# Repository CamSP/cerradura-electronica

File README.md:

# Cerradura electrónica

## Descripción del producto
El producto consiste en una cerradura electrónica casera de alta seguridad, la cuál permitirá al usuario tener 3 niveles de autenticación distintos para acceder a ella. También cuenta con la opción de registar más de un usuario previamente registrado en una base de datos. Los sensores encargados para la debida autenticación de los usuarios son: 

* Reconocimiento facial
* Huella dactilar
* Sistema RFID por tarjeta

El sistema implementará la huella dactilar y el RFID en la carcasa de la cerradura. Para el reconocimiento facial se hará uso de una aplicación con el fin de simplificar los requerimientos de hardware del producto. Adicionalmente, en la aplicación se administrará la cerradura, lo que incluye los usuarios registrados y huellas registradas en esta. Se puede configurar la cerradura para tener una única o una doble autentificación en caso de que se necesiten mayores restricciones para el manejo de la cerradura.
El elemento diferencial de nuestro producto a los demás sistemas que se encuentran en el mercado es la experiencia personal al hacer uso de varios sistemas biométricos y una aplicación que permiten al usuario interactuar de manera directa con la cerradura. Adicionalemnte, nuestro producto incluye más periféricos que las que se encuentran en el mercado, esto causa una diversificación en el uso del sistema. Otro vlor añadido es el costo vs prestaciones, ya que en el mercado cerraduras biométricas son costosas y solo poseen el lector de huellas como módulo de seguridad.

## Requerimientos funcionales
* Uso de cerradura electrónica para controlar la apertura de la puerta.
* Reconocimiento facial desde el teléfono como alternativa para abrir o cerrar la cerradura.
* Reconocimiento de huellas dactilares.
* Comunicación con base de datos remota a través de WiFi.
* Comunicación con dispositivos a través de bluetooth
* La lectura de huella dactilar y el reconocimiento facial puede realizarse por medio de la aplicación móvil.
* En caso de que haya un corte en la energía, el sistema seguirá funcionando con baterias.

## Requerimientos no funcionales
* Debido al uso de la cerradura electrónica, la cerradura mecánica convencional no es necesaria, sin embargo, en caso de que el cliente lo desee, se pueden usar en conjunto.
* Los usuarios registrados de cada cerradura no pueden ser vistos/usados por usuarios externos al propietario.
* El producto debe adaptarse a diferentes tipos de cerraduras.
* El sistema de autenticación remoto debe poder ser utilizado en la mayor cantidad de modelos de teléfonos posible.
* La aplicación móvil del dispositivo debe estar disponible en inglés y español.
* Los datos solo podrán ser cambiados por el administrador de la cerradura.
* La cerradura está pensada para uso doméstico, esto considerando que el nivel de seguridad para uso en empresas o industrias debe ser mayor.
* El sistema podrá funcionar sin necesidad de conexión a internet.
* El sistema tendra un método de autentificación para los administradores de la cerradura.
* El sistema puede repararse rapidamente cambiando uno de los modulos, ademas el daño en uno de los modulos no inhabilita el sistema.
* La caja del producto debe ser resistente a golpes.
* El sistema no podrá ser desmontado desde la parte exterior de la puerta.
* Para garantizar la seguridad de datos de los usuarios, se utilizará encriptación en la base de datos del sistema.
* En caso de cortes de energía se deshabilitarán los módulos bluetooth y WiFi para maximizar la duración de la carga de la batería.
* Se le asignará un espacio de memoria interna al dispositivo para almacenar los datos necesarios de autenticación del huella dactilar y RFID en el caso de exista un corte en la energía y no se pueda utilizar el WiFi.

## Componentes Utilizados
* Capacitores: 0.1 uF, 22 uF, 10 uF, 0.3 uF, 100 pF, 47 uF y 100 uF.
* Resistencias: 10k Ohm, 62k Ohm, 3.3k Ohm, 47k Ohm, 100 Ohm.
* Inductores: 22 uH.
* LEDs.
* Diodos Rectificadores: SS34 y 1N5406.
* Diodos.
* ESP32 - WROVER.
* Módulo RFID RC522.
* Lector de Huella AS608.
* Elevador de Voltaje MT3608.
* Regulador de Voltaje AMS1117.
* Conector 01x02.
* Conector 01x03.
* Relé Sanyou SRD Form C.
* Switch.

## Características
* Se utilizan componentes superficiales con el fin de reducir el tamaño del circuito.  
* El circuito se diseña y se programa para mininizar el gasto de energia en sí, donde el mayor gasto de la energia está en la cerradura. 
* El circuito consiste del controlador ESP32, sus protección, indicadores y conexiones a los otros periféricos, como el lector de huella.
* El diseño del circuito fue pensado para hacerse de forma modular con la cerradura y sus periféricos.

## Diseño del circuito

Primero se parte del controlador a utilizar, en este caso el esp32.
Seguidamente se determinan los módulos a utilizar, el RFID, el sensor de huella.
Con esto presente se seleccionan los pines necesarios para los módulos, además se realiza la etapa de potencia para 
la cerradura. Se realiza la pcb en kicad. Se incluyen indicadores, LEDs, para cada función (Alerta on-off, conexión establecida con cada uno de los módulos) 
Importante. El diseño también se hizo modular en el programa kicad. 
Se incluyeron los agujeros para la sujeción de la placa y se realizó la pcb en allpcb.
Se utilizaron componentes smd.

### ESP32

El controlador esp32 fue utilizado porque facilita la comunicación WiFi y Bluetooth. Además su programación es através de 
Micropython o el ide de Arduino. Esto hace rápida la programación si existen las librerías para los sensores.

### Etapa de potencia
* modulo ams1117
Regulador lineal de alta eficiencia. Dispositivo de voltaje fijo para usarlo a 3.3v con corriente maxima de 1 amperio, temperatura de trabajo de -40 150, con voltaja entrada 4.75 para una salida de 3.3. Y Pérdidas de voltaje debidas al calor.
Para una entrada de voltaje entre 4.8 y 12 V en este ams1117-3.3 se consigue 3.3 V en la salida, utilizando los capacitores recomendados por el fabricante.
* modulo mt3608
El mt3608 es un conversor DC-DC conmutado tipo boost. Trabaja de 2V a 24V en la entrada, dispositivo de voltaje de salida variable. Además de una eficiencia del 97 %. El fabricante da un circuito para aplicación basica. Este trabaja a una frecuencia fija. Para las resistencias, se utiliza la siguiente relación deacuerdo con el voltaje de entrada.
Vout=Vref*(1+R1/R2). 
Para el inductor es recomendable utilizar uno de 4.7uH a 22uH.
En cuanto a los capacitores, dos capacitores iguales de  alrededor de los 22uF.
Tambien el fabricante sugiere un diodo shcottky para no interferir con la velocidad de funcionamiento del modulo mt3608.

### Cerradura
Para el circuito de la cerradura se utiliza un rele de 3v que se conencta a una de las salidas digitales del ESP32. Entre los terminales normalmente abiertos se conecta la cerradura y 12v que la alimentan, de forma que cuando el rele se enciende se energiza la cerradura. Por otro lado, dado que el rele y la cerradura utilizan enbobinados para funcionar, es necesario proteger el circuito de posibles corrientes parasitas que estas generen una vez dejen de estar energizadas, de esta forma se conecta un diodo entre GND y la entrada digital que se conecta al rele, y otro diodo entre GND y la conexión entre el rele y la cerradura.

### RFID
Para el lector RFID se utilizó el módulo comercial que incluye el sistema de modulación y demodulación de 13.56 MHz y la respectiva antena para la lectura. El módulo se comunica por SPI por lo que puede ser utilizado con el ESP32 sin problemas. La conexión a la placa se realiza mediante una serie de puertos donde se introducen los pines del RFID; trabaja con 3.3 voltios por lo que puede ser utilizado directamente con una alimentación de 5 voltios. El pin de alimentación tiene una conexión con un condensador para proteger el módulo y de allí al relé.

### Sensor de huella

El módulo utilizado es el as608, un módulo fácil de conseguir, el cual permite una programación sensilla con las librerías existentes,
Este módulo tiene una memoria y permite guardar y verificar las huellas ingresadas, además su comunicación es serial.

### LEDS de funcionamiento

Se incluyeron LEDs como indicadores, para saber si hay batería, 
Si hay WiFi o si está abierta o cerrada la cerradura.

### Programador

La programación se hizo con micropython porque Python es un lenguaje conocido y fácil de entender, además de tener 
las librerías necesarias para el proyecto, se utizo la ide Tommy de Linux y se subieron los diferentes programas con un computador cuyo
sistema operativo es Linux. 
Para el sensor de la huella, fue necesario buscar el tipo de programación que utiliza y 
como programarlo con Python, es lo más importante, después se utilizó la libreria del sensor correspondiente
y se estudió la librería para utilizarla con dos fines, guardas huellas y verificar huellas guardadas, con el fin 
de enviar un bit y abrir la cerradura.

## Programación
Para la programación se utiliza micropython con el IDE Thonny, a partir de esto, se establecieron las siguientes clases:

### Database
Con el fin de mantener una comunicación entre la aplicación móvil fue necesario diseñar una base de datos en firestore en la que se almacena el estado de la cerradura (abierto o cerrado), los usuarios propietarios, nombre personalizado de la cerradura y un id unico del producto. Dado que en micropython no se encuentra ninguna librería con soporte para firestore, se utilizaron operaciones CRUD y por practicidad a la hora de utilizar los recursos del ESP32, se manejo una arquitectura poco eficiente para la base de datos. De esta manera, cada documento cuenta con 2 valores (nombre e id) y 2 subdocumentos donde se almacena el estado de la cerradura y la cantidad de usuarios registrados en la cerradura.

A partir de esto, se estableció la clase database con las siguientes funciones:

* __init__: 
El constructor de la clase establece el URL de la base de datos junto con su API key. Recibe los parametros id, name, user y config; los 3 primeros corresponden a datos que se almacenan en la base de datos, mientras que config hace referencia a si es la primera vez que se conecta la cerradura y es necesario crear un nuevo documento en la base de datos.

* createDB:
Recibe los argumentos user, name e id. A partir de ellos crea los documentos necesarios en la base de datos para el futuro uso de la cerradura y aplicación.

* listener:
Para tener una comunicación constante con la base de datos, la cerradura constantemente consulta el estado de esta para evidenciar los cambios realizados desde la aplicación. Normalmente este proceso se realiza con websockets, pero, dada la falta de soporte en micropython y que es un ejercicio academico se opto por un metodo más practico pero menos eficiente.

### Config:
Esta clase es la primer en se ejecutada, se encarga de configurar la cerradura, ya sea o no la primera vez que se enciende. Para ello se realiza el siguiente procedimiento:

Si es la primera vez que se utiliza la cerradura, se genera un uuid y se scanean las redes wifi disponibles en la zona, posteriormente, se ejecuta un webserver al que se puede accerder a traves del wifi. Ingresando a la dirección 192.168.4.1 se accede a un formulario donde se pregunta el nombre de la cerradura, un correo para asociarla, y la red wifi con su contraseña. Una vez que se llena el formulario, el ESP32 intenta conectarse al WiFi. Posteriormente se almacenan los datos en un archivo JSON, en caso de que la conexión falle, la cerradura se reinicia y se repide el proceso.

Si no es la primera vez que se enciende la cerradura, se lee el archivo JSON en busca del SSID y la contraseña del WiFi para ser conectados.

Con esto en mente, se utilizan las siguientes funciones:

* __init__:

El constructor inicializa ambos modos de WiFi, es decir, como una estación o como un punto de acceso, luego lee el JSON, si el valor de UUID es nulo, genera uno nuevo y posteriormente reviza el parametro config, si este esta en True llama a la función connect y establece la conexión con el WiFi. En caso de que config este en False, scannea los SSID's cercanos e inicializa el webserver.

* scan:

Realiza la busqueda de las redes cercanas y retorna sus respectivos SSID's.

* connect:
Esta función se encarga de establecer la conexión con el WiFi, recibe un SSID y una contraseña e intenta conectarse en un lapso de 10 segundos, pasado este tiempo se da por hecho de que no fue posible realizar la conexión retornando el valor de False. En caso contrario retornarpa True.

* _httpHandlerSSIDGet:
Se encarga de envíar la lista de los SSID's al webserver.

* _httpHandlerDataPost:
Recibe los datos del formulario alojado en el webserver, una vez obtenidos llama a la función connect, y si esta retorna True, guarda los valores del formulario en el JSON. Finalmente reinicia el sistema.

* runServer:
Activa el WiFi en modo access point, utiliza las 2 funciones anteriores como route handlers e inicializa el servidos con los archivos de HTML, CSS y JS contenidos en la carpeta /www. Finalmente, inicia el servidor.

* stopServer:
Detiene el servidor.

* isConnected:
Es una función para conocer el estado del WiFi en un entorno externo a la clase. Esta sera usada posteriormente en el main del sistema.

* reset:
Se encarga de restablecer la cerradura a los valores de "fabrica", reescribiendo el JSON en valores iniciales.

### HTML, CSS y JavaScript
Con el HTML y CSS se crea un formulario sencillo y agradable a la vista. Posteriormente se ejecuta un script de JavaScript el cual recibe los datos de los SSID's y genera una lista de redes disponibles en un drop down. Cuando el formulario es completado, obtiene los valores de cada campo y los almacena en un JSON para ser enviado al "backend" del webserver.

### RFID

Esta clase maneja los diferentes UUID's de las tarjetas RFID registradas en la cerradura. Hace uso de la librería mfrc522 para controlar el sensor. Para administrar y configurar la cerradura se utiliza una tarjeta de configuración, en el archivo main se observará su uso.

* __init__:
El constructor se encarga de inicializar el sensor RC522 por medio de SPI, se establece el UUID de la tarjeta de configuración y el nombre del archivo de texto que almacena los RFIDs.

* check_card_code:
Recive un UUID de un RFID, abre el archivo con la lista de RFIDs guardados y compara si este valor se encuentra en dicha lista, en caso de que si, retornará True, de lo contrario False.

* getCard:
Obtiene el UUID de la tarjeta leida.

* getSecretCard:
Retorna el valor de la tarjeta de configuración.

### Fingerprint as608
Para este sensor se utilizaron las librerias pyfingerprint y machine. pyfingerprint tiene todas las instrucciones necesarias para comunicarse con el as608, además tiene  funciones importantes para utilizar el sensor para huella, como su almacenamiento y operación. Por otro lado la libreria machine permite configurar la comunicación seria con el esp32.
La libreria contiene una clase, que es necesaria para identificar el sensor, por lo tanto se debe crear esa clase para utilizar sus métodos y así hacer las lecturas necesarias.

* verifyPasswird():
Nos permite acceder al sensor mediante su contraseña, usualmente se utiliza la constraseña de fabrica. Esto se utiliza para saber si esta conectado el sensor.
* getTemplateCount():
Este metodo nos permite saber el numero de almacenamiento de las huellas.
* getStorageCapacity():
Este método nos da información de la capacidad de almacenamiento de una huella dada.
* readImage():
Este metodo simplemente lee lo que este en la superficie del sensor.
* searchTemplate():
Este metodo busca coincidencias de una huella leida con las huellas guardades.
* convertImage():
Convierte la imagen leida en un sistema de almacenamiento diferente para ser guardado.
* createTemplate():
Combina los caracteres previamente guardados, creando un template nuevo para ser almacenado. 
* storeTemplate():
Almacena un templade en una ubicacion dado de las 255 permitidas para este sensor.

Con los anteriores métodos fue posible guardar y verificar las huellas existentes para así utilizar la cerradura.

### Main
Este es el archivo que se ejecuta cuando se inicia la cerradura, primero se establece la frecuencia y el duty cicle para el PWM de los LEDS, luego se inicializa cada uno de ellos y se establece la comunicación con el sensor de huela AS608. Luego se establecen 2 funciones para generar un parpadeo en los LEDs:

* blinkLed:
Realiza un corto blink en el led recibido.

* blinkOn:
Por medio de un hilo para que nunca se detenga, se ejecuta un blink en el led de encendido, en caso de que el WiFi este conectado, el LED de este tambien parpadeara.

Luego se utiliza la función openLock que abre la cerradura durante 3 segundos. Posteriormente se inicializa la clase config, luego se lee el archivo JSON y se inicializa la base de datos, finalmente se inicializa la clase RFID. Luego se crea un bucle infinito que esta constantemente leyendo el RFID y el sensor de huella, en caso de que haya una coincidencia se llama a la función openLock. Si la tarjeta leida es la de configuración, la siguiente tarjeta o huella leida se guardan para que posteriormente sean usadas para abrir la puerta.

### Aplicación (IOS)
La aplicación fue realizada en Swift para plataformas con IOS y IPadOS (IPhone, IPod, IPad), puesto que este lenguaje, permite de manera sencilla utilizar los sensores biometricos del dispositivo (a diferencia de otros frameworks como react-native). Luego, la app tiene como proposito ser un intermediario entre la cerradura y el usuario, muestra las cerraduras que se encuentran en propiedad de la persona, para ello, utiliza la autentificación por email de Firebase, y posteriormente realiza busquedas en los diferentes documentos de forma que se encuentren coincidencias con el correo del usuario. A partir de esto, es posible abrir la cerradura deseada por medio de la autentificación proporcionada por IOS de FaceID.Se esperaba añadir más funciones como agregar o eliminar usuarios de una cerradura, pero por razones de tiempo no fue posible.

## Carcasa y construcción
La carcasa se divide en 2 partes, interna y externa, en otras palabras, por dentro y por fuera de la puerta. En la parte interna se encuentra la PCB junto con 4 baterias AA en seríe que suministran energía a la cerradura, estas se cubren con un acrilico para proteger el circuito. La cerradura (el selenoide) se encuentra por fuera de la caja con el fin de que pueda ser ubicada en la posición que el usuario desee, de esta manera no es necesario mover todo el sistema si se quiere cambiar la posición de la cerradura. En la parte externa se encuentran el lector RFID y el sensor de huella AS608. La carcasa fue diseñada en Fusion360 y posteriormente fabricada en impresión 3D en PLA, para ello se utilizó el software CURA como slicer y una Creality Ender 3 V2 como impresora.

## Errores y observaciones

A lo largo del desarrollo de la placa para la cerradura electrónica se encontraron distintos problemas, principalmente relacionados con el circuito, algunos de ellos son:

* Se obtuvo un error en la alimentación de la cerradura. A pesar de que el conversor entrega la diferencia de potencial requerida, la corriente para su correcto funcionamiento no era suficiente. Lo anterior debido a que la conexión que realizamos en el circuito fue entre el regulador fijo de 3.3v y la cerradura, cuando lo correcto debió ser conectar el conversor directamente entre la bateria y la cerradura.

* En el diseño original no se incluyó un transistor BJT conectado al relé, esto ocasionaba un problema ya que no se estaba alimentando al mismo con suficiente corriente, esto se relacionaba con el punto anterior y el problema de distribución de energía; la solución fue conectar un transistor 2n2222 al relé, lo que mostraba su funcionamiento correctamente. La conexión del BJT se hace para mantener uno de los principios requeridos, la integración de todos los módulos en la miisma carcasa, ya que otra solución pudo ser la externalización del módulo de la cerradura, lo que impedía llevar acabo dicho principio.

* Existió un error al hacer la conexión de una bobina en el circuito, esta se conectaba directamente a un diodo para lograr su funcionamiento, sin embargo, al hacer la conexión, se puso del lado del incorrecto del diodo, por lo que al probar el circuito, esta sección no respondía. La solución a esto fue sencilla, en este caso cortar la mala conexión y esmaltar la nueva conexion de los terminales en la bobina y el diodo para ubicarlos en el lado correcto solucionó el problema. 

* Respecto al sensor para huella as608 aunque la libreria pyfingerprint permite utilizarlp correctamente, hay que configurar su comunicación de recepción y transmisión de datos, la velocidad en baudios, los bit que se van a leer por lectura y los pines que se deben usar. La velocidad y los bits utilizados en la transmisión se puede encontrar en el datasheet y debe ser los que se indican, de lo controario no trabajaria correctamente.

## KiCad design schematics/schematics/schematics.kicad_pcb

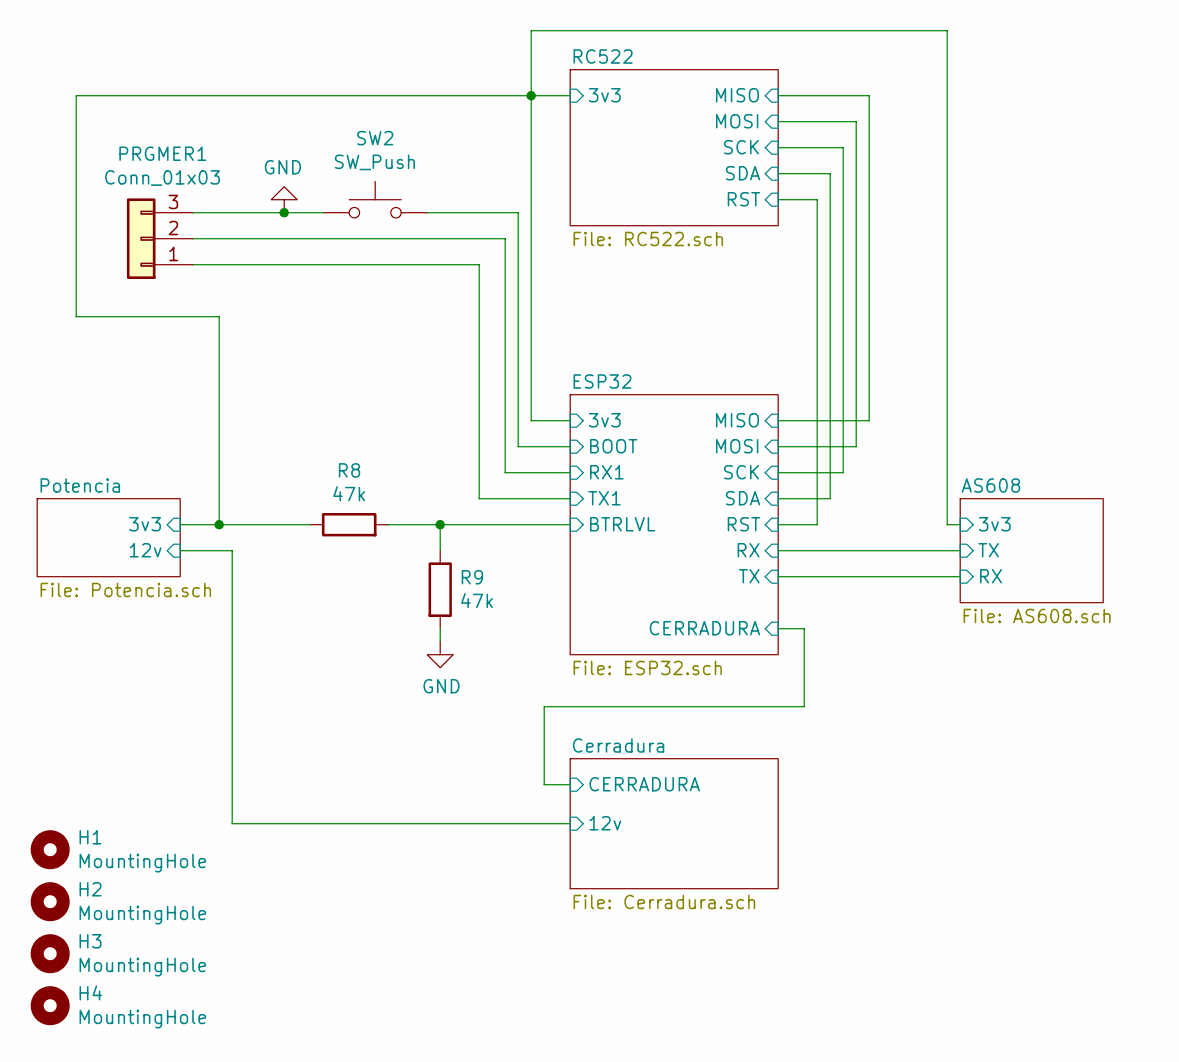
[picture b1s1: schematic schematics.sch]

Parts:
H1, H2, H3, H4: MountingHole; MountingHole_3mm
PRGMER1: Conn_01x03; PinHeader_1x03_P2.00mm_Vertical
R8, R9: 47k; R_1206_3216Metric_Pad1.42x1.75mm_HandSolder; LCSC C247434
SW2: SW_Push; SW_PUSH_6mm

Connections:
/AS608/3v3: R8.1; also elsewhere on the board
/ESP32/BOOT: SW2.2; also elsewhere on the board
/ESP32/BTRLVL: R8.2, R9.1; also elsewhere on the board
/ESP32/RX1: PRGMER1.2; also elsewhere on the board
/ESP32/TX1: PRGMER1.1; also elsewhere on the board
GND: PRGMER1.3, R9.2, SW2.1; also elsewhere on the board

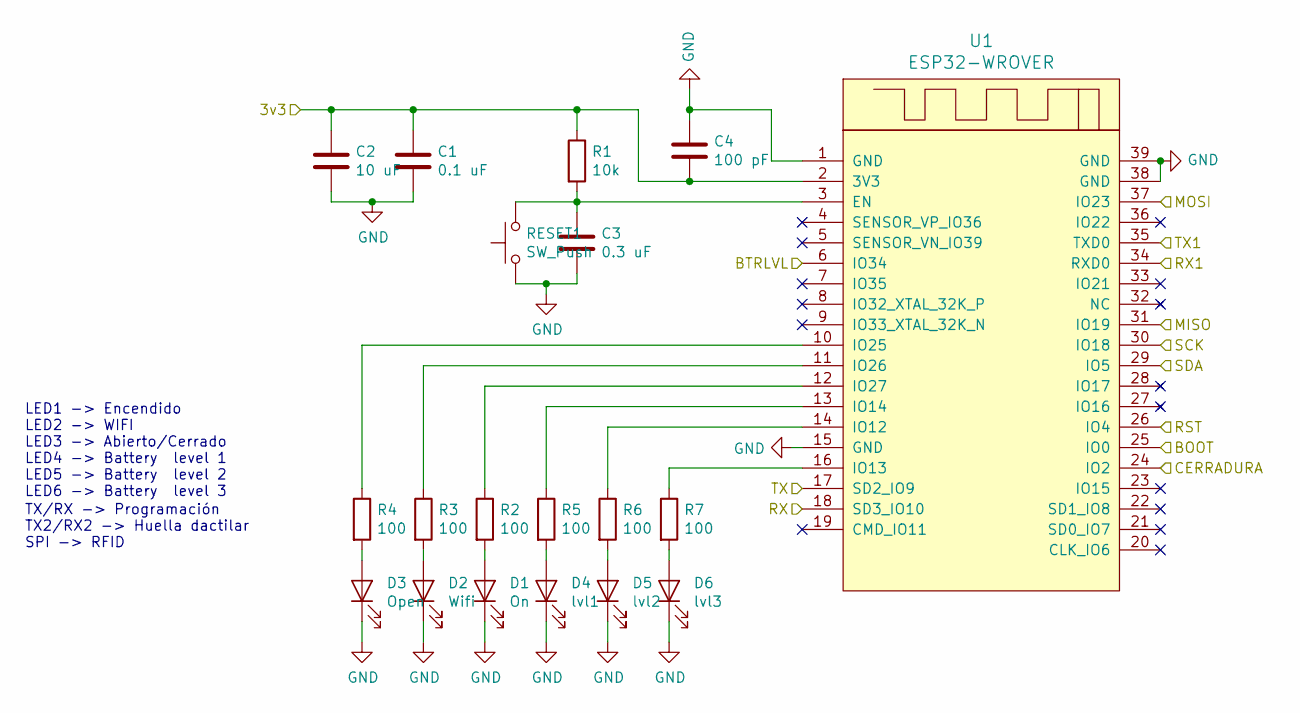
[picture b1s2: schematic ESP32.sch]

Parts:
C1: 0.1 uF; CP_Radial_D4.0mm_P2.00mm; LCSC C271438
C2: 10 uF; C_0603_1608Metric_Pad1.05x0.95mm_HandSolder; LCSC C96446
C3: 0.3 uF; CP_Radial_D5.0mm_P2.50mm
C4: 100 pF; C_0603_1608Metric_Pad1.05x0.95mm_HandSolder; LCSC C44567
D1: On; LED_0603_1608Metric_Pad1.05x0.95mm_HandSolder; LCSC C189306
D2: Wifi; LED_0603_1608Metric_Pad1.05x0.95mm_HandSolder; LCSC C375447
D3: Open; LED_0603_1608Metric_Pad1.05x0.95mm_HandSolder; LCSC C118330
D4: lvl1; LED_0603_1608Metric_Pad1.05x0.95mm_HandSolder; LCSC C375447
D5: lvl2; LED_0603_1608Metric_Pad1.05x0.95mm_HandSolder; LCSC C138546
D6: lvl3; LED_0603_1608Metric_Pad1.05x0.95mm_HandSolder; LCSC C118330
R1: 10k; R_1206_3216Metric_Pad1.42x1.75mm_HandSolder; LCSC C17902
R2, R3, R4, R5, R6, R7: 100; R_1206_3216Metric_Pad1.42x1.75mm_HandSolder; LCSC C17408
RESET1: SW_Push; boton
U1: ESP32-WROVER; XCVR_ESP32-WROVER-I; LCSC C529591

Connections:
/AS608/3v3: C1.1, C2.1, C4.2, R1.1, U1.2 (3V3); also elsewhere on the board
GND: C1.2, C2.2, C3.2, C4.1, D1.1 (K), D2.1 (K), D3.1 (K), D4.1 (K), D5.1 (K), D6.1 (K), RESET1.1, U1.1 (GND), U1.15 (GND), U1.38 (GND), U1.39 (GND); also elsewhere on the board
unnamed 16: C3.1, R1.2, RESET1.2, U1.3 (EN); also elsewhere on the board
unnamed: D1.2 (A), R2.2
unnamed: D2.2 (A), R3.2
unnamed: D3.2 (A), R4.2
unnamed: D4.2 (A), R5.2
unnamed: D5.2 (A), R6.2
unnamed: D6.2 (A), R7.2
unnamed 26: R2.1, U1.12 (IO27); also elsewhere on the board
unnamed 27: R3.1, U1.11 (IO26); also elsewhere on the board
unnamed 28: R4.1, U1.10 (IO25); also elsewhere on the board
unnamed 29: R5.1, U1.13 (IO14); also elsewhere on the board
unnamed 30: R6.1, U1.14 (IO12); also elsewhere on the board
unnamed 31: R7.1, U1.16 (IO13); also elsewhere on the board

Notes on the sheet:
TX/RX -> Programación TX2/RX2 -> Huella dactilar SPI -> RFID
LED1 -> Encendido LED2 -> WIFI LED3 -> Abierto/Cerrado LED4 -> Battery level 1 LED5 -> Battery level 2 LED6 -> Battery level 3

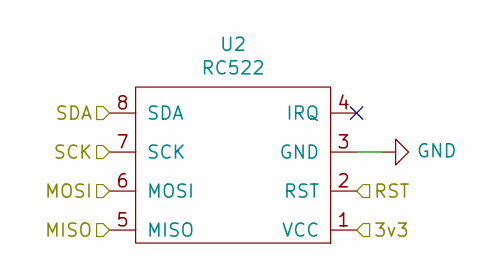
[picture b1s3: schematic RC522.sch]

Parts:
U2: RC522; JST_EH_B8B-EH-A_1x08_P2.50mm_Vertical

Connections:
/AS608/3v3: U2.1 (VCC); also elsewhere on the board
/ESP32/MISO: U2.5 (MISO); also elsewhere on the board
/ESP32/MOSI: U2.6 (MOSI); also elsewhere on the board
/ESP32/RST: U2.2 (RST); also elsewhere on the board
/ESP32/SCK: U2.7 (SCK); also elsewhere on the board
/ESP32/SDA: U2.8 (SDA); also elsewhere on the board
GND: U2.3 (GND); also elsewhere on the board

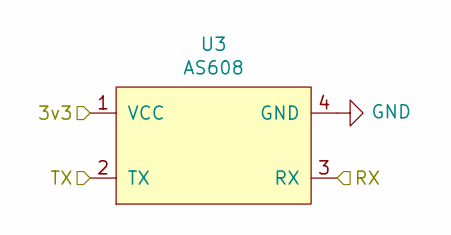
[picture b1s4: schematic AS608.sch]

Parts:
U3: AS608; JST_EH_B4B-EH-A_1x04_P2.50mm_Vertical; LCSC C144395

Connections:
/AS608/3v3: U3.1 (VCC); also elsewhere on the board
/AS608/RX: U3.3 (RX); also elsewhere on the board
/ESP32/RX: U3.2 (TX); also elsewhere on the board
GND: U3.4 (GND); also elsewhere on the board

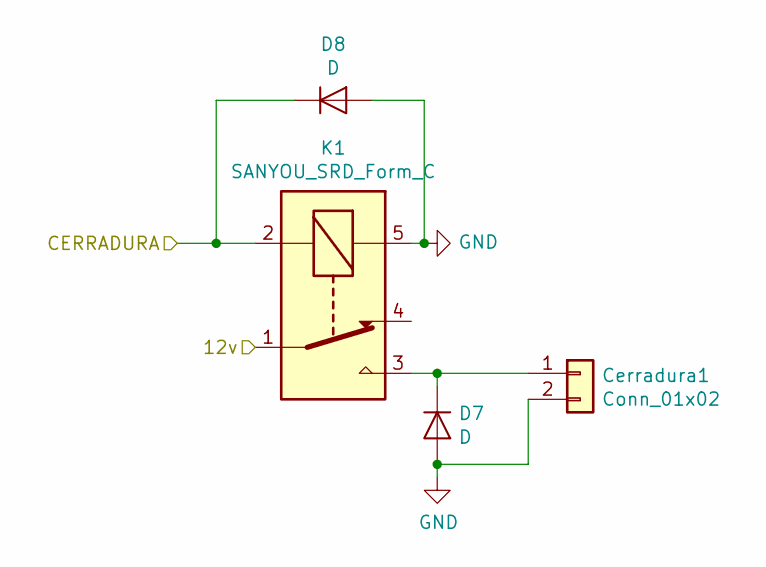
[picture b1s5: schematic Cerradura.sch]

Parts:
Cerradura1: Conn_01x02; JST_EH_B2B-EH-A_1x02_P2.50mm_Vertical; LCSC C158012
D7, D8: D; D_1206_3216Metric_Pad1.42x1.75mm_HandSolder
K1: SANYOU_SRD_Form_C; Relay_SPDT_SANYOU_SRD_Series_Form_C

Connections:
/Cerradura/12v: K1.1; also elsewhere on the board
/Cerradura/CERRADURA: D8.1 (K), K1.2; also elsewhere on the board
GND: Cerradura1.2, D7.2 (A), D8.2 (A), K1.5; also elsewhere on the board
unnamed: Cerradura1.1, D7.1 (K), K1.3

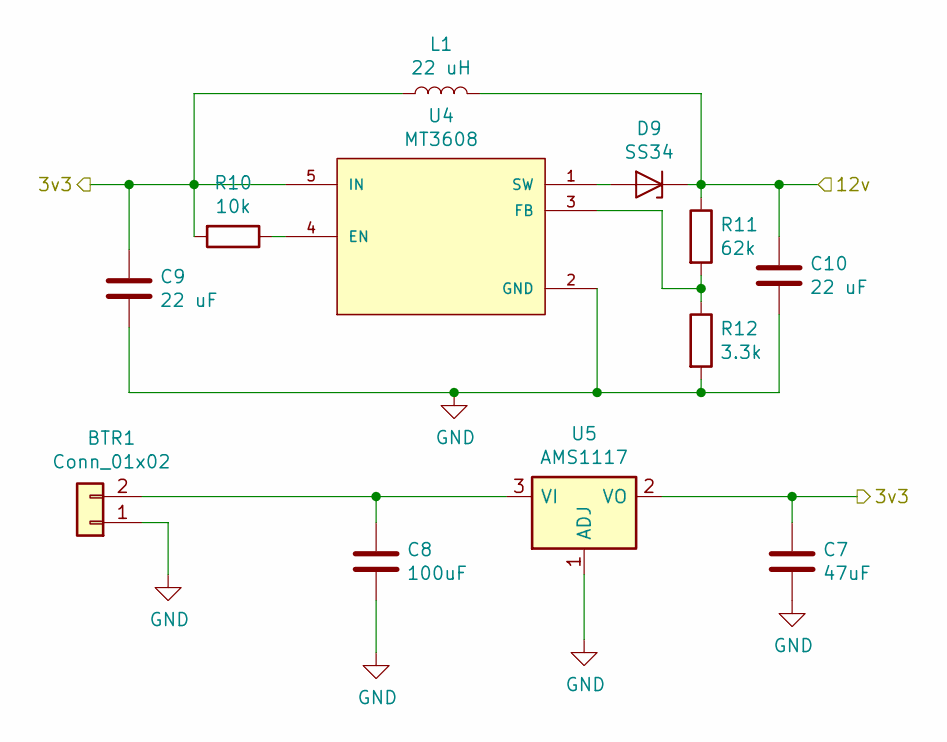
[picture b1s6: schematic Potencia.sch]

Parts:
BTR1: Conn_01x02; JST_EH_B2B-EH-A_1x02_P2.50mm_Vertical; LCSC C158012
C7: 47uF; C_0603_1608Metric_Pad1.05x0.95mm_HandSolder; LCSC C140782
C8: 100uF; CP_Radial_D5.0mm_P2.50mm
C9: 22 uF; C_0603_1608Metric_Pad1.05x0.95mm_HandSolder; LCSC C458915
C10: 22 uF; C_0603_1608Metric_Pad1.05x0.95mm_HandSolder; LCSC C140720
D9: SS34; D_SMA; LCSC C8678
L1: 22 uH; IND_RLS-226-R; LCSC C354567
R10: 10k; R_1206_3216Metric_Pad1.42x1.75mm_HandSolder; LCSC C17902
R11: 62k; R_1206_3216Metric_Pad1.42x1.75mm_HandSolder; LCSC C66032
R12: 3.3k; R_1206_3216Metric_Pad1.42x1.75mm_HandSolder; LCSC C26032
U4: MT3608; mt3608; PARTREV 1.0; LCSC C84817
U5: AMS1117; SOT-223-3_TabPin2; LCSC C6186

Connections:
/AS608/3v3: C7.1, C9.2, L1.1, R10.2, U4.5 (IN), U5.2 (VO); also elsewhere on the board
/Cerradura/12v: C10.1, D9.1 (K), L1.2, R11.1; also elsewhere on the board
GND: BTR1.1, C7.2, C8.2, C9.1, C10.2, R12.2, U4.2 (GND), U5.1 (ADJ); also elsewhere on the board
unnamed: BTR1.2, C8.1, U5.3 (VI)
unnamed: D9.2 (A), U4.1 (SW)
unnamed: R10.1, U4.4 (EN)
unnamed: R11.2, R12.1, U4.3 (FB)

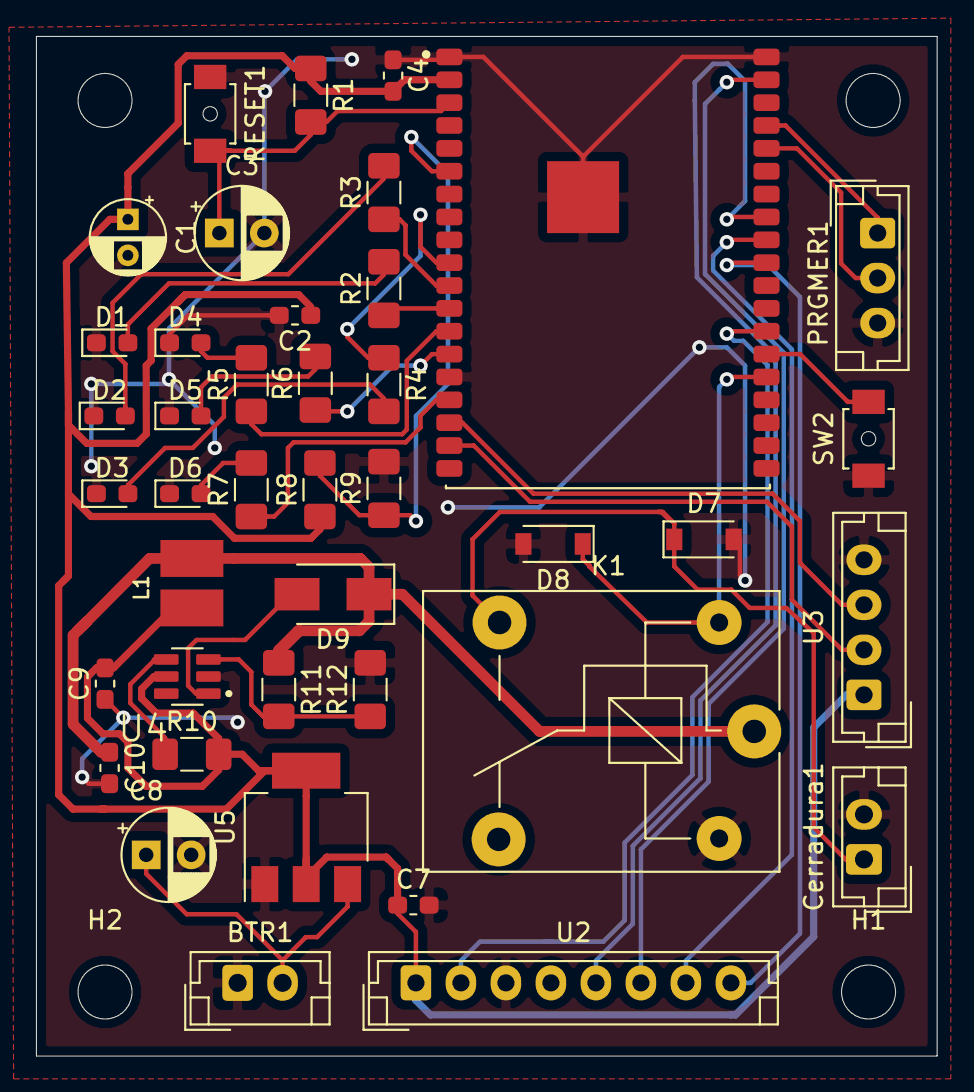
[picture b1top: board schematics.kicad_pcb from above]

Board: 2 copper layers, 50.0 x 56.6 mm, 45 parts (0 on the bottom side), 33 nets.

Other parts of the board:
 : MountingHole_3mm
  : ESP32-WROVER; XCVR_ESP32-WROVER-I
 #2: MountingHole_3mm

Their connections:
/AS608/3v3: .2; also elsewhere on the board
/AS608/RX: .17; also elsewhere on the board
/Cerradura/CERRADURA: .24; also elsewhere on the board
/ESP32/BOOT: .25; also elsewhere on the board
/ESP32/BTRLVL: .6; also elsewhere on the board
/ESP32/MISO: .31; also elsewhere on the board
/ESP32/MOSI: .37; also elsewhere on the board
/ESP32/RST: .26; also elsewhere on the board
/ESP32/RX: .18; also elsewhere on the board
/ESP32/RX1: .34; also elsewhere on the board
/ESP32/SCK: .30; also elsewhere on the board
/ESP32/SDA: .29; also elsewhere on the board
/ESP32/TX1: .35; also elsewhere on the board
GND: .1, .15, .38, .39; also elsewhere on the board
unnamed 16: .3; also elsewhere on the board
unnamed 26: .12; also elsewhere on the board
unnamed 27: .11; also elsewhere on the board
unnamed 28: .10; also elsewhere on the board
unnamed 29: .13; also elsewhere on the board
unnamed 30: .14; also elsewhere on the board
unnamed 31: .16; also elsewhere on the board

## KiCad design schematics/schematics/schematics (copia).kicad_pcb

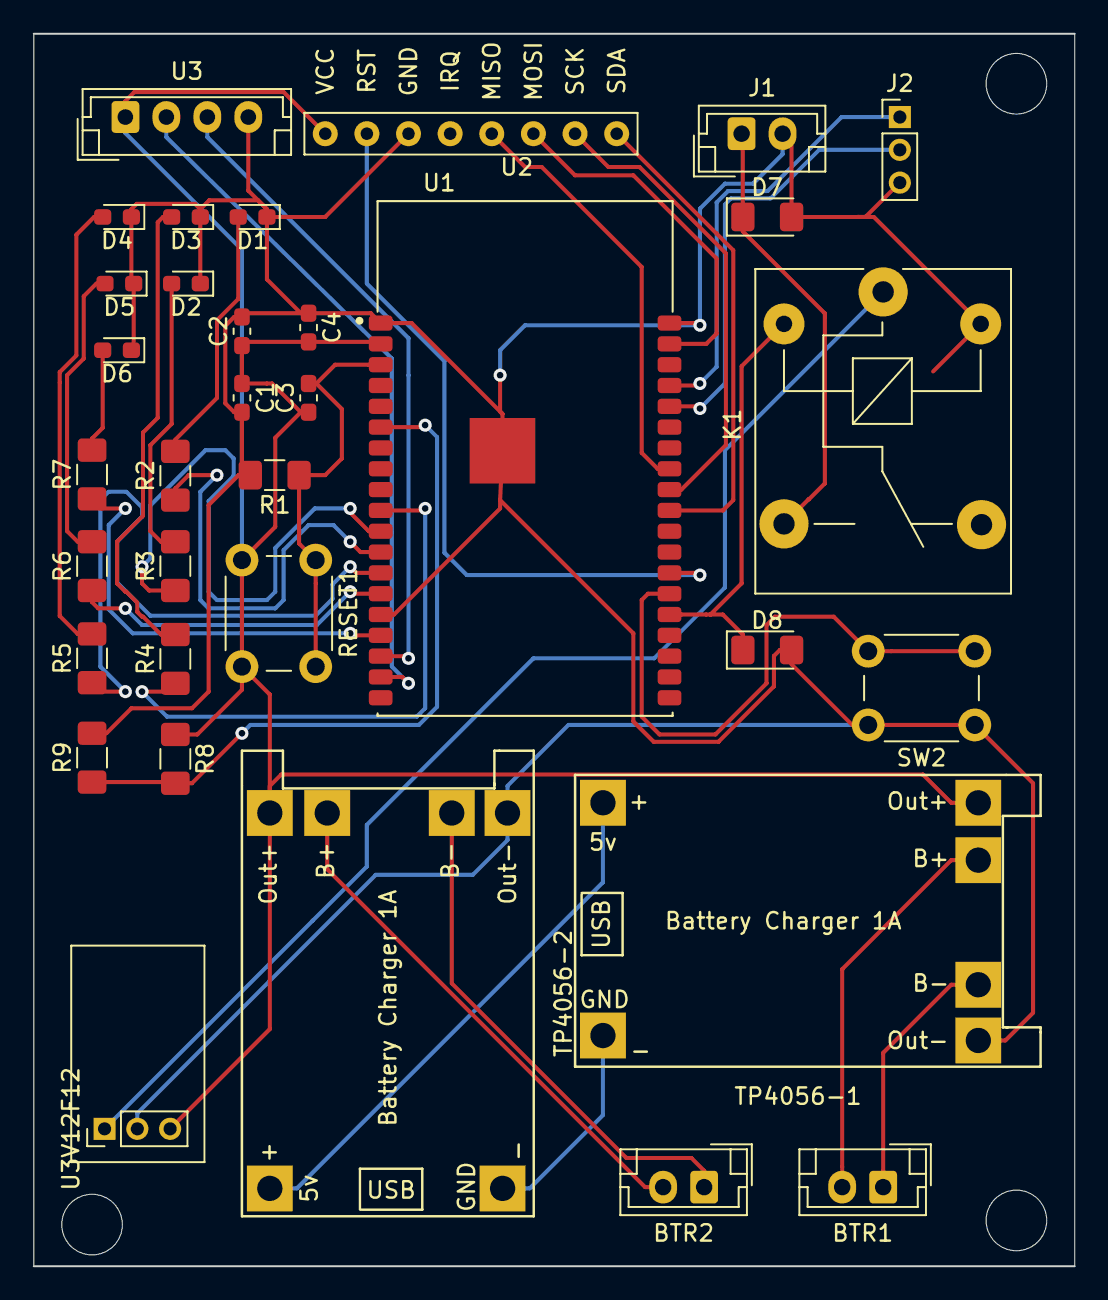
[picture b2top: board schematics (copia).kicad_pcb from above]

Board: 2 copper layers, 63.5 x 75.2 mm, 34 parts (0 on the bottom side), 35 nets.

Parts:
BTR1, BTR2: Conn_01x02; JST_EH_B2B-EH-A_1x02_P2.50mm_Vertical
C1: 0.1 uF; C_0603_1608Metric_Pad1.05x0.95mm_HandSolder
C2: 10 uF; C_0603_1608Metric_Pad1.05x0.95mm_HandSolder
C3: 0.3 uF; C_0603_1608Metric_Pad1.05x0.95mm_HandSolder
C4: C; C_0603_1608Metric_Pad1.05x0.95mm_HandSolder
D1, D2, D3, D4, D5, D6: LED; LED_0603_1608Metric_Pad1.05x0.95mm_HandSolder
D7, D8: D; D_1206_3216Metric_Pad1.42x1.75mm_HandSolder
J1: Conn_01x02; JST_EH_B2B-EH-A_1x02_P2.50mm_Vertical
J2: Conn_01x03; PinHeader_1x03_P2.00mm_Vertical
K1: SANYOU_SRD_Form_C; Relay_SPDT_SANYOU_SRD_Series_Form_C
R1: 10k; R_1206_3216Metric_Pad1.42x1.75mm_HandSolder
R2, R3, R4, R5, R6, R7: 220; R_1206_3216Metric_Pad1.42x1.75mm_HandSolder
R8, R9: 47k; R_1206_3216Metric_Pad1.42x1.75mm_HandSolder
RESET1: SW_Push; SW_PUSH_6mm
SW2: SW_Push; SW_PUSH_6mm
TP4056-1, TP4056-2: TP4056-18650
U1: ESP32-WROVER; XCVR_ESP32-WROVER-I
U2: RC522
U3: AS608; JST_EH_B4B-EH-A_1x04_P2.50mm_Vertical
U3V12F12: PinHeader_1x03_P2.00mm_Vertical

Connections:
/AS608/3v3: C1.1, C2.1, C3.1, C4.2, R8.1, RESET1.2, TP4056-1.3, TP4056-2.3, U1.2, U2.1, U3.1, U3V12F12.3
/AS608/RX: U1.17, U3.3
/Cerradura/12v: K1.1, U3V12F12.1
/Cerradura/CERRADURA: D8.1, K1.2, U1.24
/ESP32/BOOT: SW2.2, U1.25
/ESP32/BTRLVL: R8.2, R9.1, U1.6
/ESP32/MISO: U1.31, U2.5
/ESP32/MOSI: U1.37, U2.6
/ESP32/RST: U1.26, U2.2
/ESP32/RX: U1.18, U3.2
/ESP32/RX1: J2.2, U1.34
/ESP32/SCK: U1.30, U2.7
/ESP32/SDA: U1.29, U2.8
/ESP32/TX1: J2.1, U1.35
/Potencia/BTR1+: BTR1.2, TP4056-1.5
/Potencia/BTR1-: BTR1.1, TP4056-1.6
/Potencia/BTR2+: BTR2.2, TP4056-2.5
/Potencia/BTR2-: BTR2.1, TP4056-2.6
GND: C1.2, C2.2, C4.1, D1.1, D2.1, D3.1, D4.1, D5.1, D6.1, D7.2, D8.2, J1.2, J2.3, K1.5, R1.2, R9.2, SW2.1, TP4056-1.4, TP4056-2.4, U1.1, U1.15, U1.38, U1.39, U2.3, U3.4, U3V12F12.2
unnamed: C3.2, R1.1, RESET1.1, U1.3
unnamed: D1.2, R2.2
unnamed: D2.2, R3.2
unnamed: D3.2, R4.2
unnamed: D4.2, R5.2
unnamed: D5.2, R6.2
unnamed: D6.2, R7.2
unnamed: D7.1, J1.1, K1.3
unnamed: R2.1, U1.12
unnamed: R3.1, U1.11
unnamed: R4.1, U1.10
unnamed: R5.1, U1.13
unnamed: R6.1, U1.14
unnamed: R7.1, U1.16
unnamed: TP4056-1.1, TP4056-2.1
unnamed: TP4056-1.2, TP4056-2.2

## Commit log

2021-11-04 datasheets
2022-02-10 app update
